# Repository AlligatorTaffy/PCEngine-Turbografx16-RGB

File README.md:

# RGB Video for PCEngine/TurboGrafx16

As the title implies, this is a board designed in CadSoft Eagle that allows native RGB signal out for SCART.

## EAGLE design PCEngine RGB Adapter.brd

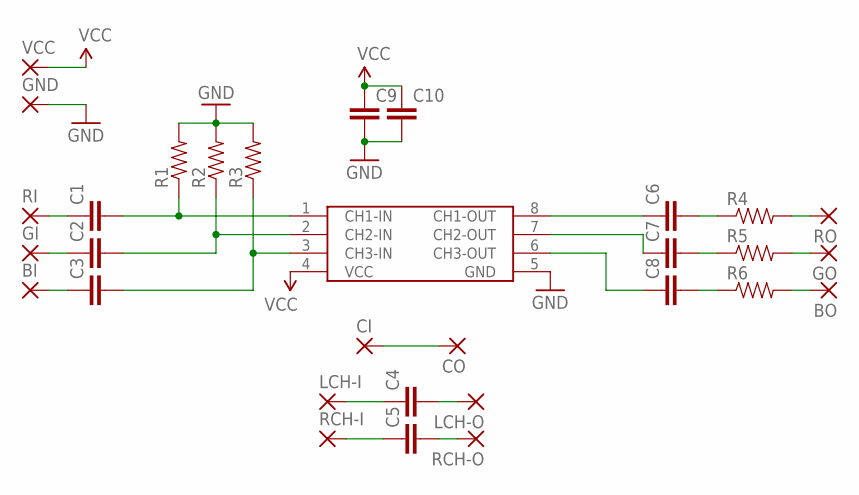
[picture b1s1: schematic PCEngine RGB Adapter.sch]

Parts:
BI: WIREPADSMD1,27-254; SMD1,27-2,54
BO: WIREPADSMD1,27-254; SMD1,27-2,54
C1, C2, C3, C4, C5, C9, C10: CAP0805; 0805
C6, C7, C8: CAP1210; 1210
CI: WIREPADSMD1,27-254; SMD1,27-2,54
CO: WIREPADSMD1,27-254; SMD1,27-2,54
GI: WIREPADSMD1,27-254; SMD1,27-2,54
GND: WIREPADSMD1,27-254; SMD1,27-2,54
GO: WIREPADSMD1,27-254; SMD1,27-2,54
LCH-I: WIREPADSMD1,27-254; SMD1,27-2,54
LCH-O: WIREPADSMD1,27-254; SMD1,27-2,54
R1, R2, R3, R4, R5, R6: RESISTOR0805-RES; 0805
RCH-I: WIREPADSMD1,27-254; SMD1,27-2,54
RCH-O: WIREPADSMD1,27-254; SMD1,27-2,54
RI: WIREPADSMD1,27-254; SMD1,27-2,54
RO: WIREPADSMD1,27-254; SMD1,27-2,54
U$1: THS7314SMD; SOIC8
VCC: WIREPADSMD1,27-254; SMD1,27-2,54

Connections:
GND: C9.2, C10.2, GND.1, R1.2, R2.2, R3.2, U$1.5 (GND)
unnamed: C1.1, RI.1
unnamed: C2.1, GI.1
unnamed: BI.1, C3.1
unnamed: C4.1, LCH-I.1
unnamed: C5.1, RCH-I.1
unnamed: C1.2, R1.1, U$1.1 (CH1-IN)
unnamed: C2.2, R2.1, U$1.2 (CH2-IN)
unnamed: C3.2, R3.1, U$1.3 (CH3-IN)
unnamed: C6.1, U$1.8 (CH1-OUT)
unnamed: C6.2, R4.1
unnamed: R4.2, RO.1
unnamed: GO.1, R5.2
unnamed: C7.2, R5.1
unnamed: C7.1, U$1.7 (CH2-OUT)
unnamed: C8.1, U$1.6 (CH3-OUT)
unnamed: C8.2, R6.1
unnamed: BO.1, R6.2
unnamed: C5.2, RCH-O.1
unnamed: C4.2, LCH-O.1
unnamed: CI.1, CO.1
VCC: C9.1, C10.1, U$1.4 (VCC), VCC.1

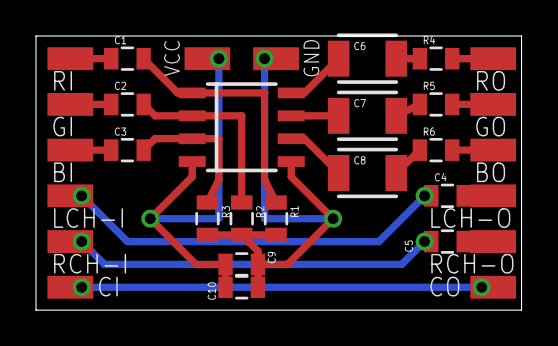
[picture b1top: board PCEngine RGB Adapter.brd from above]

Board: 2 copper layers, 27.0 x 15.2 mm, 31 parts (0 on the bottom side), 22 nets.

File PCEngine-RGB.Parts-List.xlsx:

PCEngine RGB AMP Parts List
Name | Value | Package | Digikey Part # | Notes
R1 - Note 1 | 5.1M | 0805 | 311-5.1MARCT-ND | Note 1
R2 - Note 1 | 5.1M | 0805 | 311-5.1MARCT-ND | 5.1M resistors replaced the
R3 - Note 1 | 5.1M | 0805 | 311-5.1MARCT-ND | original 3.6M resistors.
R4 | 75 | 0805 | 311-75.0CRCT-ND
R5 | 75 | 0805 | 311-75.0CRCT-ND
R6 | 75 | 0805 | 311-75.0CRCT-ND
C1 - Note 2 | 0.1uF | 0805 | 1276-1007-1-ND | Note 2
C2 - Note 2 | 0.1uF | 0805 | 1276-1007-1-ND | 0.1uF capacitors replaced
C3 - Note 2 | 0.1uF | 0805 | 1276-1007-1-ND | the original 82nF capacitors.
C4 | 1uF | 0805 | 1276-1066-1-ND
C5 | 1uF | 0805 | 1276-1066-1-ND | Note 3
C6 - Note 3 | 220uF | 1210 | 1276-3375-1-ND | 220uF capacitors replaced
C7 - Note 3 | 220uF | 1210 | 1276-3375-1-ND | the original 330uF capacitors.
C8 - Note 3 | 220uF | 1210 | 1276-3375-1-ND
C9 | 22uF | 0805 | 1276-2910-1-ND
C10 - Optional | 0.1uF | 0805 | 1276-1007-1-ND
THS7314DR |  | SOIC8 | 296-26683-1-ND
 |  |  |  | PJEJJ 2014
Parts were replaced to closely match the original datasheet. Can use the origin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

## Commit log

2023-05-29 Migrate sources to GitHub

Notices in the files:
parts and their libraries:
SparkFun-Capacitors: Licensing: Creative Commons ShareAlike 4.0 International - https://creativecommons.org/licenses/by-sa/4.0
